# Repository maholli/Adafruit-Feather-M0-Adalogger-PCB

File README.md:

# **lab64 version** of *Adafruit-Feather-M0-Adalogger-PCB*

Part subs, package changes, and additional silkscreen for improved solderability. 

KiCAD layout files for the SAMD21 board with microSD.

### Major changes
* 48-QFN subbed for 48-QFP. Easier soldering/rework for workshops
* different microUSB receptacle
* different microSD receptacle
* different JTAG test point layout
* increased board width by 0.01" to allow GND plane to flow

<br>
<br>
<br>
<br>
<br>
<br>
<br>
<br>

------
For more details, check out the product page at

  * https://www.adafruit.com/product/2796

Adafruit invests time and resources providing this open source design, 
please support Adafruit and open-source hardware by purchasing 
products from Adafruit!

Designed by Adafruit Industries.  
Creative Commons Attribution, Share-Alike license, check license.txt for more information
All text above must be included in any redistribution

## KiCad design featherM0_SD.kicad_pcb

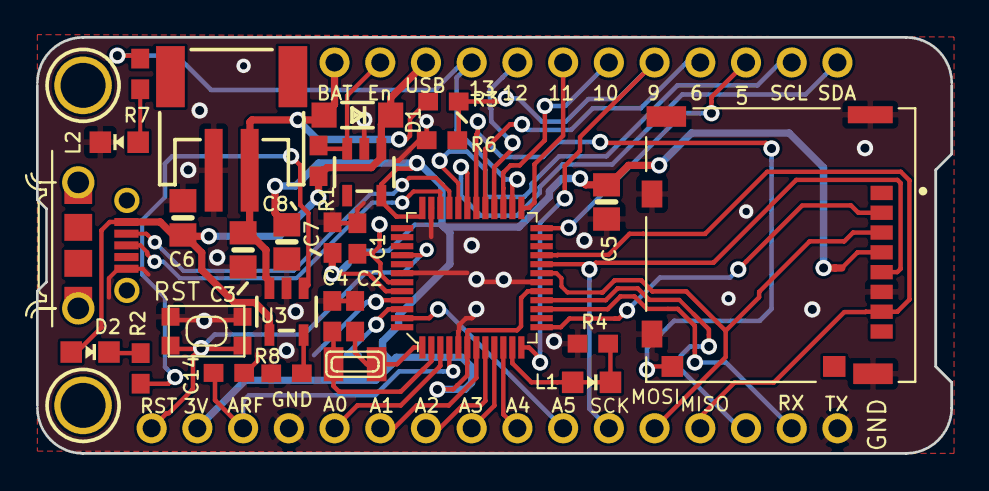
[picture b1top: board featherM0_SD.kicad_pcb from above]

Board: 2 copper layers, 50.8 x 23.1 mm, 34 parts (0 on the bottom side), 41 nets.

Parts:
C1, C7, C14: 1uF; 0603-NO
C2, C4: 22pF; 0603-NO
C3, C6, C8: 10µF; 0805-NO
C5: 10uF; 0805-NO
D1: MBR120; SOD-123
D2: ORANGE; CHIPLED_0805_NOOUTLINE
J1: 10118194-0001LF; FRAMATOME_10118194-0001LF
J2: 503182-1853; MOLEX_503182-1853
JP1: HEADER-1X16ROUND; 1X16_ROUND
JP3: HEADER-1X12; 1X12_ROUND
L1: GREEN; CHIPLED_0805_NOOUTLINE
L2: RED; CHIPLED_0805_NOOUTLINE
R1, R3: 100k; 0603-NO
R2, R4: 1K; 0603-NO
R6: 100K; 0603-NO
R7: 2.2K; 0603-NO
R8: 10K\; 0603-NO
SW1: SPST_TACT-KMR2; KMR2
TP1, TP2: TESTPOINTROUND1.5MM; TESTPOINT_ROUND_1.5MM
U1: ATSAMD21G18A-AUT; TQFP-48_7x7mm
U2: SPX3819-3.3; SOT23-5
U3: MCP73831T-2ACI/OT; SOT23-5
U$31, U$32: MOUNTINGHOLE2.5; MOUNTINGHOLE_2.5_PLATED
X1: JSTPH; JSTPH2
X2: 32.768; XTAL3215

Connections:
+3V3: C5.1, C7.1, C8.1, J2.4, JP1.15, U1.6, U1.17, U1.36, U1.44, U2.5
/A0: JP1.12, U1.3
/A1: JP1.11, U1.7
/A2: JP1.10, U1.8
/A3: JP1.9, U1.9
/A4: JP1.8, U1.10
/A5: JP1.7, U1.47
/AREF: C14.1, JP1.14, U1.4
/D0: JP1.3, U1.16
/D1: JP1.2, U1.15
/D5: JP3.10, U1.24
/D6: JP3.9, U1.29
/D7: J2.DET_T, U1.30
/D8: L1.A, L1.C, R4.1, U1.11
/D9: JP3.8, R3.2, R6.1, U1.12
/D10: JP3.7, U1.27
/D11: JP3.6, U1.25
/D12: JP3.5, U1.28
/D13: JP3.4, R7.1, U1.26
/EN: JP3.2, R1.2, U2.3
/MISO: J2.7, JP1.4, U1.21
/MOSI: J2.3, JP1.5, U1.19
/SCK: J2.5, JP1.6, U1.20
/SCL: JP3.11, U1.32
/SDA: JP3.12, U1.31
/SD_CS: J2.2, U1.13
/SWCLK: TP1.P$1, U1.45
/SWDIO: TP2.P$1, U1.46
/~RESET: JP1.16, SW1.1, SW1.3, U1.40
GND: C1.2, C2.2, C3.2, C4.2, C5.2, C6.2, C7.2, C8.2, C14.2, J1.5, J2.6, J2.SH1, J2.SH2, J2.SH3, J2.SH4, J2.SH5, JP1.1, JP1.13, L2.C, R4.2, R6.2, R8.2, SW1.2, SW1.4, U1.5, U1.18, U1.35, U1.42, U2.2, U3.2, X1.1
unnamed: C1.1, U1.43
unnamed: C2.1, U1.1, X2.P$1
unnamed: C4.1, U1.2, X2.P$2
unnamed: D2.C, R2.1
unnamed: J1.2, U1.33
unnamed: J1.3, U1.34
unnamed: L2.A, R7.2
unnamed: R2.2, U3.1
unnamed: R8.1, U3.5
VBAT: C3.1, D1.A, JP3.1, R3.1, U3.3, X1.2
VBUS: C6.1, D1.C, D2.A, J1.1, JP3.3, R1.1, U2.1, U3.4

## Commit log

2018-10-18 migrating changes to Adafruit fork
2018-10-18 readme clarification
2018-10-20 cleaned up silkscreen
2018-10-20 added logo
2018-10-22 cleaned up board outline
